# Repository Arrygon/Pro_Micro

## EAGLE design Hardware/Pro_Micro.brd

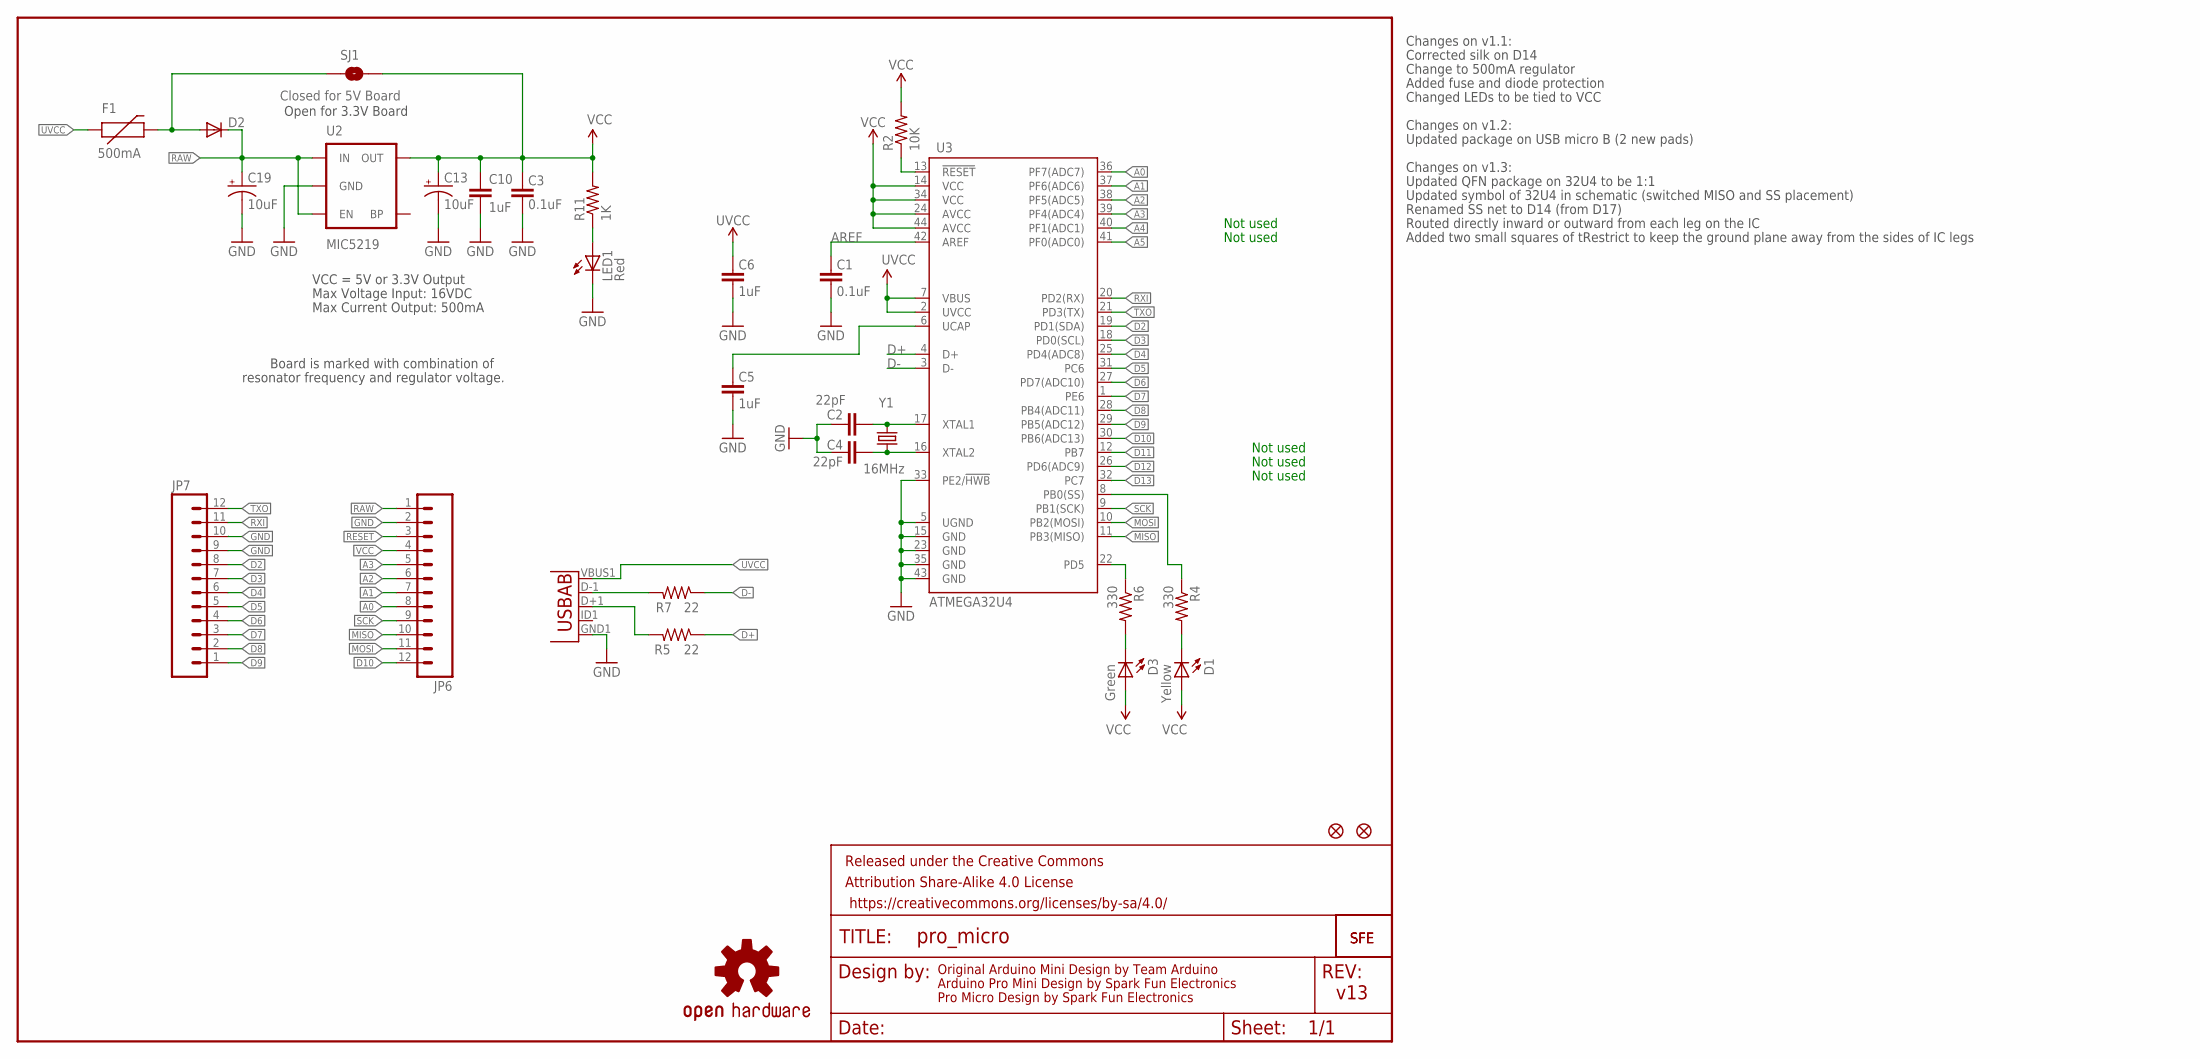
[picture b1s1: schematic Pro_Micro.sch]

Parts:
C1, C3: 0.1uF; 0603-CAP
C2, C4: 22pF; 0603-CAP
C5, C6, C10: 1uF; 0603-CAP
C13, C19: 10uF; EIA3216
D1: Yellow; LED-0603
D2: DIODESOD; SOD-323
D3: Green; LED-0603
F1: 500mA; PTC-1206
FRAME1: FRAME-LETTER; CREATIVE_COMMONS
JP1, JP2: FIDUCIALUFIDUCIAL; MICRO-FIDUCIAL
JP6, JP7: M12PTH; 1X12
LED1: Red; LED-0603
R2: 10K; 0603-RES
R4, R6: 330; 0603-RES
R5, R7: 22; 0603-RES
R11: 1K; 0603-RES
SJ1: Closed for 5V Board; SJ_2S
U2: MIC5219; SOT23-5
U3: ATMEGA32U4; QFN-44-NOPAD_1:1-LESS_PASTE
U$1: LOGO-SFESK; SFE-LOGO-FLAME
U$3: OSHW-LOGOS; OSHW-LOGO-S
U$11: LOGO-SFENEW; SFE-NEW-WEBLOGO
X1: USB-ABIN&OUT; USB-AB-MICRO-SMD-V03-IN&OUT
Y1: 16MHz; CRYSTAL-SMD-5X3

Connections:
A0: JP6.8, U3.36 (PF7(ADC7))
A1: JP6.7, U3.37 (PF6(ADC6))
A2: JP6.6, U3.38 (PF5(ADC5))
A3: JP6.5, U3.39 (PF4(ADC4))
A4: U3.40 (PF1(ADC1))
A5: U3.41 (PF0(ADC0))
AREF: C1.2, U3.42 (AREF)
D2: JP7.8, U3.19 (PD1(SDA))
D3: JP7.7, U3.18 (PD0(SCL))
D4: JP7.6, U3.25 (PD4(ADC8))
D5: JP7.5, U3.31 (PC6)
D6: JP7.4, U3.27 (PD7(ADC10))
D7: JP7.3, U3.1 (PE6)
D8: JP7.2, U3.28 (PB4(ADC11))
D9: JP7.1, U3.29 (PB5(ADC12))
D10: JP6.12, U3.30 (PB6(ADC13))
D11: U3.12 (PB7)
D12: U3.26 (PD6(ADC9))
D13: U3.32 (PC7)
D17: R4.1, U3.8 (PB0(SS))
D+: R5.1, U3.4 (D+)
D-: R7.1, U3.3 (D-)
GND: C1.1, C2.2, C3.1, C4.2, C5.1, C6.1, C10.2, C13.C (-), C19.C (-), JP6.2, JP7.9, JP7.10, LED1.C, U2.2 (GND), U3.5 (UGND), U3.15 (GND), U3.23 (GND), U3.33 (PE2/!HWB), U3.35 (GND), U3.43 (GND), X1.GND1 (GND)
MISO: JP6.10, U3.11 (PB3(MISO))
MOSI: JP6.11, U3.10 (PB2(MOSI))
unnamed: C4.1, U3.16 (XTAL2), Y1.1
unnamed: C2.1, U3.17 (XTAL1), Y1.3 (2)
unnamed: D2.2 (A), F1.2, SJ1.1
unnamed: C5.2, U3.6 (UCAP)
unnamed: D1.C, R4.2
unnamed: R7.2, X1.D-1 (D-)
unnamed: D3.C, R6.2
unnamed: R5.2, X1.D+1 (D+)
unnamed: LED1.A, R11.1
RAW: C19.A (+), D2.1 (C), JP6.1, U2.1 (IN), U2.3 (EN)
RESET: JP6.3, R2.1, U3.13 (!RESET)
RXI: JP7.11, U3.20 (PD2(RX))
SCK: JP6.9, U3.9 (PB1(SCK))
TXLED: R6.1, U3.22 (PD5)
TXO: JP7.12, U3.21 (PD3(TX))
UVCC: C6.2, F1.1, U3.2 (UVCC), U3.7 (VBUS), X1.VBUS1 (VBUS)
VCC: C3.2, C10.1, C13.A (+), D1.A, D3.A, JP6.4, R2.2, R11.2, SJ1.2, U2.5 (OUT), U3.14 (VCC), U3.24 (AVCC), U3.34 (VCC), U3.44 (AVCC)

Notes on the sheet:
Original Arduino Mini Design by Team Arduino
Arduino Pro Mini Design by Spark Fun Electronics
Max Voltage Input: 16VDC
Max Current Output: 500mA
Board is marked with combination of
resonator frequency and regulator voltage.
VCC = 5V or 3.3V Output
Not used
Pro Micro Design by Spark Fun Electronics
Changes on v1.1:
Corrected silk on D14
Change to 500mA regulator
Open for 3.3V Board
Added fuse and diode protection
Changed LEDs to be tied to VCC
Changes on v1.2:
Updated package on USB micro B (2 new pads)
Changes on v1.3:
Updated QFN package on 32U4 to be 1:1
Updated symbol of 32U4 in schematic (switched MISO and SS placement)
Renamed SS net to D14 (from D17)
Routed directly inward or outward from each leg on the IC
Added two small squares of tRestrict to keep the ground plane away from the sides of IC legs
v13

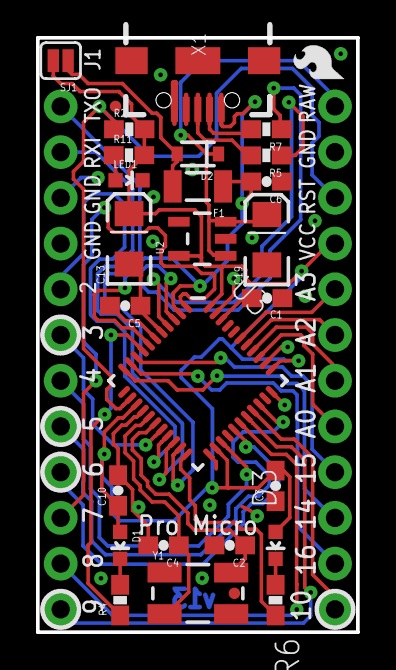
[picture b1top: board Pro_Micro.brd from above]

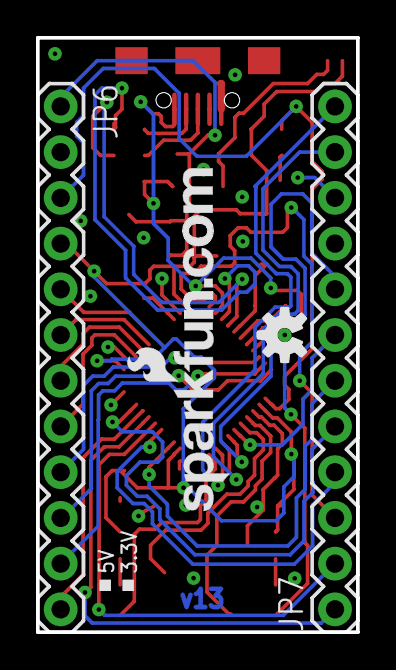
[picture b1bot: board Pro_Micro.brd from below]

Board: 2 copper layers, 17.8 x 33.0 mm, 33 parts (4 on the bottom side), 37 nets.

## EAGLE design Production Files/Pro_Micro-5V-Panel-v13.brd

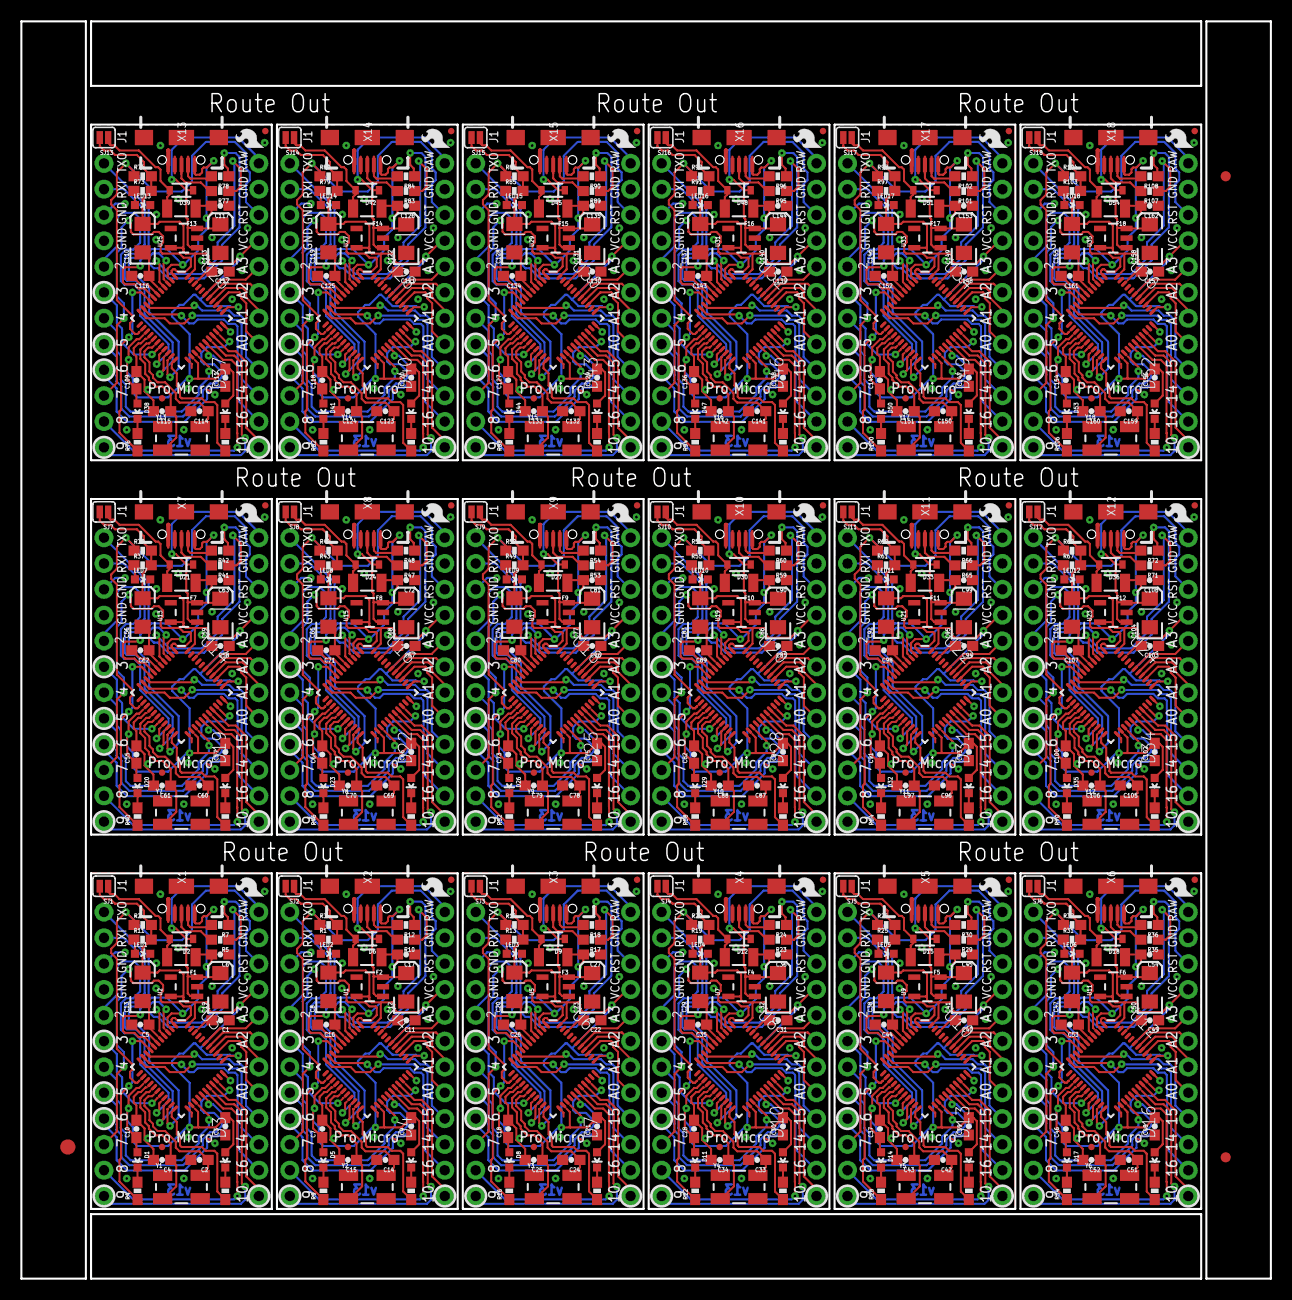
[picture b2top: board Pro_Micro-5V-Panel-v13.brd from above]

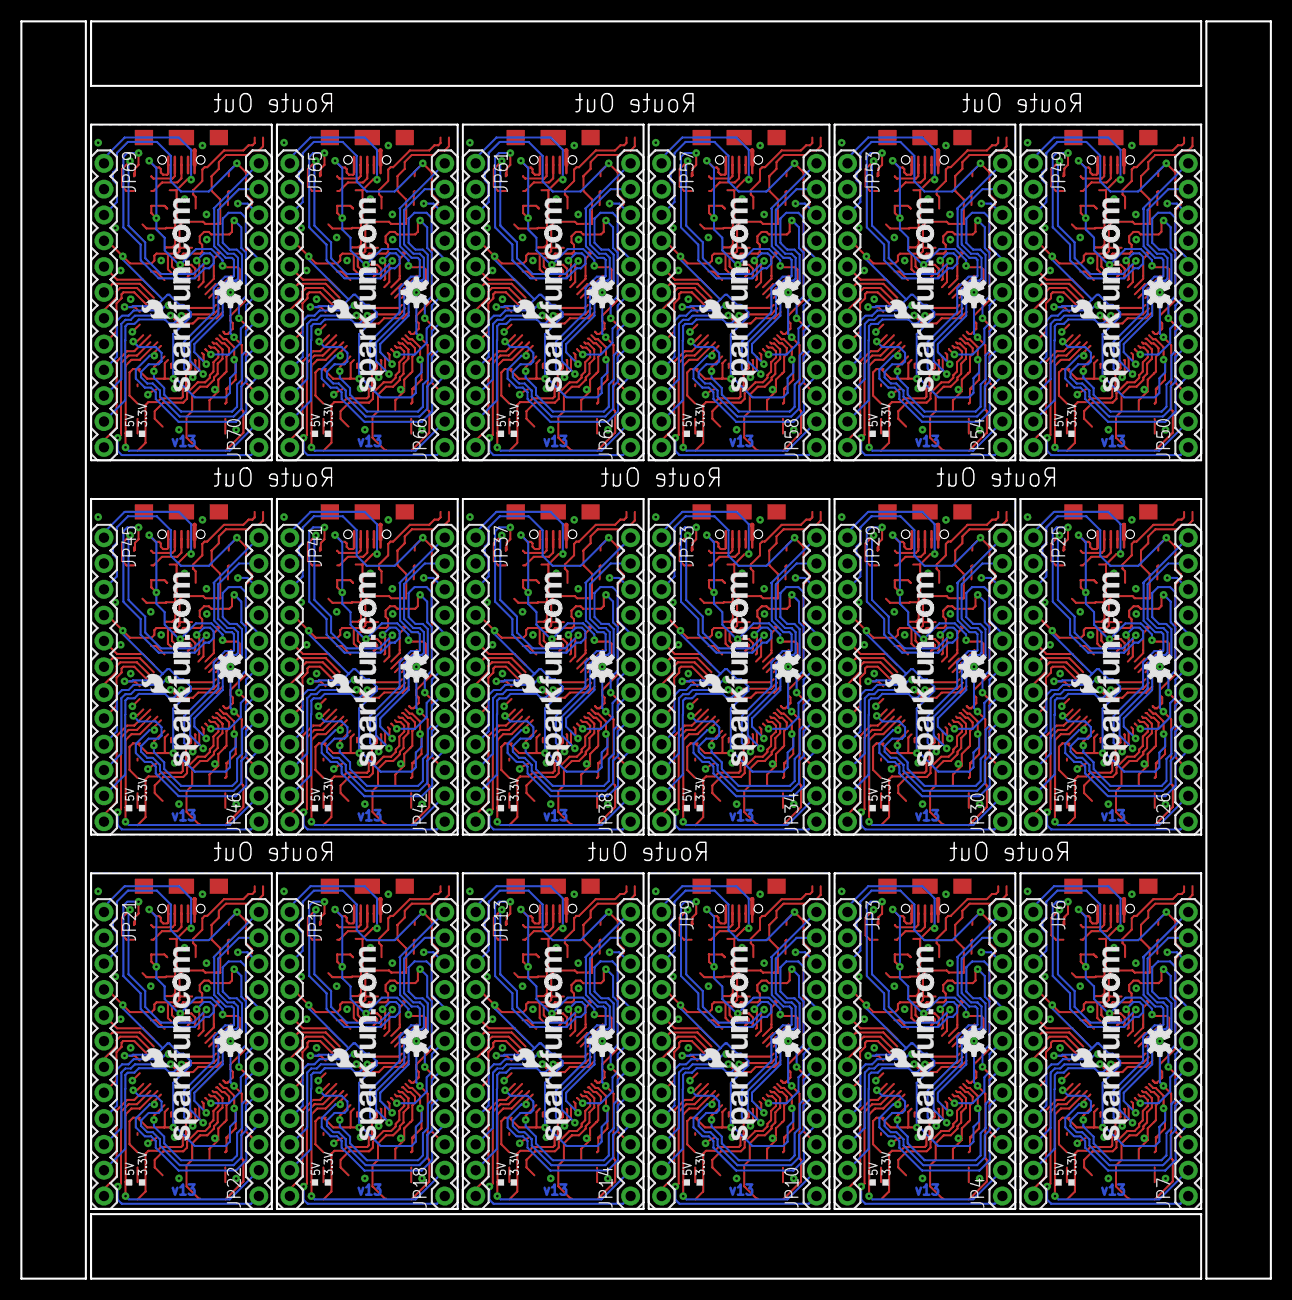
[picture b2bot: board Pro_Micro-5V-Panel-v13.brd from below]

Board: 2 copper layers, 122.9 x 123.7 mm, 579 parts (72 on the bottom side), 666 nets.

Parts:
C1, C3, C9, C11, C21, C22, C30, C31, C39, C40, C48, C49, C57, C58, C66, C67, C75, C76, C84, C85, C93, C94, C102, C103, C111, C112, C120, C121, C129, C130, C138, C139, C147, C148, C156, C157: 0.1uF; 0603-CAP
C2, C4, C14, C15, C24, C25, C33, C34, C42, C43, C51, C52, C60, C61, C69, C70, C78, C79, C87, C88, C96, C97, C105, C106, C114, C115, C123, C124, C132, C133, C141, C142, C150, C151, C159, C160: 22pF; 0603-CAP
C5, C6, C7, C10, C16, C17, C18, C26, C27, C28, C35, C36, C37, C44, C45, C46, C53, C54, C55, C62, C63, C64, C71, C72, C73, C80, C81, C82, C89, C90, C91, C98, C99, C100, C107, C108, C109, C116, C117, C118, C125, C126, C127, C134, C135, C136, C143, C144, C145, C152, C153, C154, C161, C162: 1uF; 0603-CAP
C8, C12, C13, C19, C20, C23, C29, C32, C38, C41, C47, C50, C56, C59, C65, C68, C74, C77, C83, C86, C92, C95, C101, C104, C110, C113, C119, C122, C128, C131, C137, C140, C146, C149, C155, C158: 10uF; EIA3216
D1, D5, D8, D11, D14, D17, D20, D23, D26, D29, D32, D35, D38, D41, D44, D47, D50, D53: Yellow; LED-0603
D2, D6, D9, D12, D15, D18, D21, D24, D27, D30, D33, D36, D39, D42, D45, D48, D51, D54: SOD-323
D3, D4, D7, D10, D13, D16, D19, D22, D25, D28, D31, D34, D37, D40, D43, D46, D49, D52: Green; LED-0603
E$1: FIDUCIAL-1.5X3
E$4, E$6: FIDUCIAL-1X2
F1, F2, F3, F4, F5, F6, F7, F8, F9, F10, F11, F12, F13, F14, F15, F16, F17, F18: 500mA; PTC-1206
JP1, JP2, JP5, JP8, JP11, JP12, JP15, JP16, JP19, JP20, JP23, JP24, JP27, JP28, JP31, JP32, JP35, JP36, JP39, JP40, JP43, JP44, JP47, JP48, JP51, JP52, JP55, JP56, JP59, JP60, JP63, JP64, JP67, JP68, JP71, JP72: FIDUCIALUFIDUCIAL; MICRO-FIDUCIAL
JP3, JP4, JP6, JP7, JP9, JP10, JP13, JP14, JP17, JP18, JP21, JP22, JP25, JP26, JP29, JP30, JP33, JP34, JP37, JP38, JP41, JP42, JP45, JP46, JP49, JP50, JP53, JP54, JP57, JP58, JP61, JP62, JP65, JP66, JP69, JP70: 1X12
LED1, LED2, LED3, LED4, LED5, LED6, LED7, LED8, LED9, LED10, LED11, LED12, LED13, LED14, LED15, LED16, LED17, LED18: Red; LED-0603
R1, R11, R13, R19, R25, R31, R37, R43, R49, R55, R61, R67, R73, R79, R85, R91, R97, R103: 1K; 0603-RES
R2, R3, R14, R20, R26, R32, R38, R44, R50, R56, R62, R68, R74, R80, R86, R92, R98, R104: 10K; 0603-RES
R4, R6, R8, R9, R15, R16, R21, R22, R27, R28, R33, R34, R39, R40, R45, R46, R51, R52, R57, R58, R63, R64, R69, R70, R75, R76, R81, R82, R87, R88, R93, R94, R99, R100, R105, R106: 330; 0603-RES
R5, R7, R10, R12, R17, R18, R23, R24, R29, R30, R35, R36, R41, R42, R47, R48, R53, R54, R59, R60, R65, R66, R71, R72, R77, R78, R83, R84, R89, R90, R95, R96, R101, R102, R107, R108: 22; 0603-RES
SJ1, SJ2, SJ3, SJ4, SJ5, SJ6, SJ7, SJ8, SJ9, SJ10, SJ11, SJ12, SJ13, SJ14, SJ15, SJ16, SJ17, SJ18: Closed for 5V Board; SJ_2S
U1, U2, U5, U7, U9, U11, U13, U15, U17, U19, U21, U23, U25, U27, U29, U31, U33, U35: MIC5219; SOT23-5
U3, U4, U6, U8, U10, U12, U14, U16, U18, U20, U22, U24, U26, U28, U30, U32, U34, U36: ATMEGA32U4; QFN-44-NOPAD_1:1-LESS_PASTE
U$1, U$4, U$7, U$10, U$14, U$17, U$20, U$23, U$26, U$29, U$32, U$35, U$38, U$41, U$44, U$47, U$50, U$53: LOGO-SFESK; SFE-LOGO-FLAME
U$2, U$6, U$9, U$11, U$13, U$16, U$19, U$22, U$25, U$28, U$31, U$34, U$37, U$40, U$43, U$46, U$49, U$52: LOGO-SFENEW; SFE-NEW-WEBLOGO
U$3, U$5, U$8, U$12, U$15, U$18, U$21, U$24, U$27, U$30, U$33, U$36, U$39, U$42, U$45, U$48, U$51, U$54: OSHW-LOGOS; OSHW-LOGO-S
X1, X2, X3, X4, X5, X6, X7, X8, X9, X10, X11, X12, X13, X14, X15, X16, X17, X18: USB-AB-MICRO-SMD-V03-IN&OUT
Y1, Y2, Y3, Y4, Y5, Y6, Y7, Y8, Y9, Y10, Y11, Y12, Y13, Y14, Y15, Y16, Y17, Y18: 16MHz; CRYSTAL-SMD-5X3

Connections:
A0: JP6.8, U3.36
A1: JP6.7, U3.37
A2: JP6.6, U3.38
A3: JP6.5, U3.39
A8: JP3.5, U4.39
A9: JP3.6, U4.38
A10: JP3.7, U4.37
A11: JP3.8, U4.36
A14: JP9.5, U6.39
A15: JP9.6, U6.38
A16: JP9.7, U6.37
A17: JP9.8, U6.36
A20: JP13.5, U8.39
A21: JP13.6, U8.38
A22: JP13.7, U8.37
A23: JP13.8, U8.36
A26: JP17.5, U10.39
A27: JP17.6, U10.38
A28: JP17.7, U10.37
A29: JP17.8, U10.36
A32: JP21.5, U12.39
A33: JP21.6, U12.38
A34: JP21.7, U12.37
A35: JP21.8, U12.36
A38: JP25.5, U14.39
A39: JP25.6, U14.38
A40: JP25.7, U14.37
A41: JP25.8, U14.36
A44: JP29.5, U16.39
A45: JP29.6, U16.38
A46: JP29.7, U16.37
A47: JP29.8, U16.36
A50: JP33.5, U18.39
A51: JP33.6, U18.38
A52: JP33.7, U18.37
A53: JP33.8, U18.36
A56: JP37.5, U20.39
A57: JP37.6, U20.38
A58: JP37.7, U20.37
A59: JP37.8, U20.36
A62: JP41.5, U22.39
A63: JP41.6, U22.38
A64: JP41.7, U22.37
A65: JP41.8, U22.36
A68: JP45.5, U24.39
A69: JP45.6, U24.38
A70: JP45.7, U24.37
A71: JP45.8, U24.36
A74: JP49.5, U26.39
A75: JP49.6, U26.38
A76: JP49.7, U26.37
A77: JP49.8, U26.36
A80: JP53.5, U28.39
A81: JP53.6, U28.38
A82: JP53.7, U28.37
A83: JP53.8, U28.36
A86: JP57.5, U30.39
A87: JP57.6, U30.38
A88: JP57.7, U30.37
A89: JP57.8, U30.36
A92: JP61.5, U32.39
A93: JP61.6, U32.38
A94: JP61.7, U32.37
A95: JP61.8, U32.36
A98: JP65.5, U34.39
A99: JP65.6, U34.38
A100: JP65.7, U34.37
A101: JP65.8, U34.36
A104: JP69.5, U36.39
A105: JP69.6, U36.38
A106: JP69.7, U36.37
A107: JP69.8, U36.36
AREF: C1.2, U3.42
AREF1: C11.2, U4.42
AREF2: C22.2, U6.42
AREF3: C31.2, U8.42
AREF4: C40.2, U10.42
AREF5: C49.2, U12.42
AREF6: C58.2, U14.42
AREF7: C67.2, U16.42
AREF8: C76.2, U18.42
AREF9: C85.2, U20.42
AREF10: C94.2, U22.42
AREF11: C103.2, U24.42
AREF12: C112.2, U26.42
AREF13: C121.2, U28.42
AREF14: C130.2, U30.42
AREF15: C139.2, U32.42
AREF16: C148.2, U34.42
AREF17: C157.2, U36.42
D1: JP4.1, U4.29
D2: JP7.8, U3.19
D3: JP7.7, U3.18
D4: JP7.6, U3.25
D5: JP7.5, U3.31
D6: JP7.4, U3.27
D7: JP7.3, U3.1
D8: JP7.2, U3.28
D9: JP7.1, U3.29
D10: JP6.12, U3.30
D14: R4.1, U3.8
D15: JP4.2, U4.28
D16: JP4.8, U4.19
D17: JP4.7, U4.18
D18: JP4.6, U4.25
D19: JP4.5, U4.31
D20: JP4.4, U4.27
D21: JP4.3, U4.1
D22: JP3.12, U4.30
D26: R9.1, U4.8
D27: JP10.1, U6.29
D28: JP10.2, U6.28
D29: JP10.8, U6.19
D30: JP10.7, U6.18
D31: JP10.6, U6.25
D32: JP10.5, U6.31
D33: JP10.4, U6.27
D34: JP10.3, U6.1
D35: JP9.12, U6.30
D39: R16.1, U6.8
D40: JP14.1, U8.29
D41: JP14.2, U8.28
D42: JP14.8, U8.19
D43: JP14.7, U8.18
D44: JP14.6, U8.25
D45: JP14.5, U8.31
D46: JP14.4, U8.27
D47: JP14.3, U8.1
D48: JP13.12, U8.30
D52: R22.1, U8.8
D53: JP18.1, U10.29
D54: JP18.2, U10.28
D55: JP18.8, U10.19
D56: JP18.7, U10.18
D57: JP18.6, U10.25
D58: JP18.5, U10.31
D59: JP18.4, U10.27
D60: JP18.3, U10.1
D61: JP17.12, U10.30
D65: R28.1, U10.8
D66: JP22.1, U12.29
D67: JP22.2, U12.28
D68: JP22.8, U12.19
D69: JP22.7, U12.18
D70: JP22.6, U12.25
D71: JP22.5, U12.31
D72: JP22.4, U12.27
D73: JP22.3, U12.1
D74: JP21.12, U12.30
D78: R34.1, U12.8
D79: JP26.1, U14.29
D80: JP26.2, U14.28
D81: JP26.8, U14.19
D82: JP26.7, U14.18
D83: JP26.6, U14.25
D84: JP26.5, U14.31
D85: JP26.4, U14.27
D86: JP26.3, U14.1
D87: JP25.12, U14.30
D91: R40.1, U14.8
D92: JP30.1, U16.29
D93: JP30.2, U16.28
D94: JP30.8, U16.19
D95: JP30.7, U16.18
D96: JP30.6, U16.25
D97: JP30.5, U16.31
D98: JP30.4, U16.27
D99: JP30.3, U16.1
D100: JP29.12, U16.30
D104: R46.1, U16.8
D105: JP34.1, U18.29
D106: JP34.2, U18.28
D107: JP34.8, U18.19
D108: JP34.7, U18.18
D109: JP34.6, U18.25
D110: JP34.5, U18.31
D111: JP34.4, U18.27
D112: JP34.3, U18.1
D113: JP33.12, U18.30
D117: R52.1, U18.8
D118: JP38.1, U20.29
D119: JP38.2, U20.28
D120: JP38.8, U20.19
D121: JP38.7, U20.18
D122: JP38.6, U20.25
D123: JP38.5, U20.31
D124: JP38.4, U20.27
D125: JP38.3, U20.1
D126: JP37.12, U20.30
D130: R58.1, U20.8
D131: JP42.1, U22.29
D132: JP42.2, U22.28
D133: JP42.8, U22.19
D134: JP42.7, U22.18
D135: JP42.6, U22.25
D136: JP42.5, U22.31
D137: JP42.4, U22.27
D138: JP42.3, U22.1
D139: JP41.12, U22.30
D143: R64.1, U22.8
D144: JP46.1, U24.29
D145: JP46.2, U24.28
D146: JP46.8, U24.19
D147: JP46.7, U24.18
D148: JP46.6, U24.25
D149: JP46.5, U24.31
D150: JP46.4, U24.27
D151: JP46.3, U24.1
D152: JP45.12, U24.30
D156: R70.1, U24.8
D157: JP50.1, U26.29
D158: JP50.2, U26.28
D159: JP50.8, U26.19
D160: JP50.7, U26.18
D161: JP50.6, U26.25
D162: JP50.5, U26.31
D163: JP50.4, U26.27
D164: JP50.3, U26.1
D165: JP49.12, U26.30
D169: R76.1, U26.8
D170: JP54.1, U28.29
D171: JP54.2, U28.28
D172: JP54.8, U28.19
D173: JP54.7, U28.18
D174: JP54.6, U28.25
D175: JP54.5, U28.31
D176: JP54.4, U28.27
D177: JP54.3, U28.1
D178: JP53.12, U28.30
D182: R82.1, U28.8
D183: JP58.1, U30.29
D184: JP58.2, U30.28
D185: JP58.8, U30.19
D186: JP58.7, U30.18
D187: JP58.6, U30.25
D188: JP58.5, U30.31
D189: JP58.4, U30.27
D190: JP58.3, U30.1
D191: JP57.12, U30.30
D195: R88.1, U30.8
D196: JP62.1, U32.29
D197: JP62.2, U32.28
D198: JP62.8, U32.19
D199: JP62.7, U32.18
D200: JP62.6, U32.25
D201: JP62.5, U32.31
D202: JP62.4, U32.27
D203: JP62.3, U32.1
D204: JP61.12, U32.30
D208: R94.1, U32.8
D209: JP66.1, U34.29
D210: JP66.2, U34.28
D211: JP66.8, U34.19
D212: JP66.7, U34.18
D213: JP66.6, U34.25
D214: JP66.5, U34.31
D215: JP66.4, U34.27
D216: JP66.3, U34.1
D217: JP65.12, U34.30
D221: R100.1, U34.8
D222: JP70.1, U36.29
D223: JP70.2, U36.28
D224: JP70.8, U36.19
D225: JP70.7, U36.18
D226: JP70.6, U36.25
D227: JP70.5, U36.31
D228: JP70.4, U36.27
D229: JP70.3, U36.1
D230: JP69.12, U36.30
D234: R106.1, U36.8
D+: R5.1, U3.4
D+1: R10.1, U4.4
D+2: R17.1, U6.4
D+3: R23.1, U8.4
D+4: R29.1, U10.4
D+5: R35.1, U12.4
D+6: R41.1, U14.4
D+7: R47.1, U16.4
D+8: R53.1, U18.4
D+9: R59.1, U20.4
D+10: R65.1, U22.4
D+11: R71.1, U24.4
D+12: R77.1, U26.4
D+13: R83.1, U28.4
D+14: R89.1, U30.4
D+15: R95.1, U32.4
D+16: R101.1, U34.4
D+17: R107.1, U36.4
D-: R7.1, U3.3
D-1: R12.1, U4.3
D-2: R18.1, U6.3
D-3: R24.1, U8.3
D-4: R30.1, U10.3
D-5: R36.1, U12.3
D-6: R42.1, U14.3
D-7: R48.1, U16.3
D-8: R54.1, U18.3
D-9: R60.1, U20.3
D-10: R66.1, U22.3
D-11: R72.1, U24.3
D-12: R78.1, U26.3
D-13: R84.1, U28.3
D-14: R90.1, U30.3
D-15: R96.1, U32.3
D-16: R102.1, U34.3
D-17: R108.1, U36.3
GND: C1.1, C2.2, C3.1, C4.2, C5.1, C6.1, C10.2, C13.C, C19.C, JP6.2, JP7.9, JP7.10, LED1.C, U2.2, U3.5, U3.15, U3.23, U3.33, U3.35, U3.43, X1.GND1
GND1: C7.2, C8.C, C9.1, C11.1, C12.C, C14.2, C15.2, C16.1, C17.1, JP3.2, JP4.9, JP4.10, LED2.C, U1.2, U4.5, U4.15, U4.23, U4.33, U4.35, U4.43, X2.GND1
GND2: C18.2, C20.C, C21.1, C22.1, C23.C, C24.2, C25.2, C26.1, C27.1, JP9.2, JP10.9, JP10.10, LED3.C, U5.2, U6.5, U6.15, U6.23, U6.33, U6.35, U6.43, X3.GND1
GND3: C28.2, C29.C, C30.1, C31.1, C32.C, C33.2, C34.2, C35.1, C36.1, JP13.2, JP14.9, JP14.10, LED4.C, U7.2, U8.5, U8.15, U8.23, U8.33, U8.35, U8.43, X4.GND1
GND4: C37.2, C38.C, C39.1, C40.1, C41.C, C42.2, C43.2, C44.1, C45.1, JP17.2, JP18.9, JP18.10, LED5.C, U9.2, U10.5, U10.15, U10.23, U10.33, U10.35, U10.43, X5.GND1
GND5: C46.2, C47.C, C48.1, C49.1, C50.C, C51.2, C52.2, C53.1, C54.1, JP21.2, JP22.9, JP22.10, LED6.C, U11.2, U12.5, U12.15, U12.23, U12.33, U12.35, U12.43, X6.GND1
GND6: C55.2, C56.C, C57.1, C58.1, C59.C, C60.2, C61.2, C62.1, C63.1, JP25.2, JP26.9, JP26.10, LED7.C, U13.2, U14.5, U14.15, U14.23, U14.33, U14.35, U14.43, X7.GND1
GND7: C64.2, C65.C, C66.1, C67.1, C68.C, C69.2, C70.2, C71.1, C72.1, JP29.2, JP30.9, JP30.10, LED8.C, U15.2, U16.5, U16.15, U16.23, U16.33, U16.35, U16.43, X8.GND1
GND8: C73.2, C74.C, C75.1, C76.1, C77.C, C78.2, C79.2, C80.1, C81.1, JP33.2, JP34.9, JP34.10, LED9.C, U17.2, U18.5, U18.15, U18.23, U18.33, U18.35, U18.43, X9.GND1
GND9: C82.2, C83.C, C84.1, C85.1, C86.C, C87.2, C88.2, C89.1, C90.1, JP37.2, JP38.9, JP38.10, LED10.C, U19.2, U20.5, U20.15, U20.23, U20.33, U20.35, U20.43, X10.GND1
GND10: C91.2, C92.C, C93.1, C94.1, C95.C, C96.2, C97.2, C98.1, C99.1, JP41.2, JP42.9, JP42.10, LED11.C, U21.2, U22.5, U22.15, U22.23, U22.33, U22.35, U22.43, X11.GND1
GND11: C100.2, C101.C, C102.1, C103.1, C104.C, C105.2, C106.2, C107.1, C108.1, JP45.2, JP46.9, JP46.10, LED12.C, U23.2, U24.5, U24.15, U24.23, U24.33, U24.35, U24.43, X12.GND1
GND12: C109.2, C110.C, C111.1, C112.1, C113.C, C114.2, C115.2, C116.1, C117.1, JP49.2, JP50.9, JP50.10, LED13.C, U25.2, U26.5, U26.15, U26.23, U26.33, U26.35, U26.43, X13.GND1
GND13: C118.2, C119.C, C120.1, C121.1, C122.C, C123.2, C124.2, C125.1, C126.1, JP53.2, JP54.9, JP54.10, LED14.C, U27.2, U28.5, U28.15, U28.23, U28.33, U28.35, U28.43, X14.GND1
GND14: C127.2, C128.C, C129.1, C130.1, C131.C, C132.2, C133.2, C134.1, C135.1, JP57.2, JP58.9, JP58.10, LED15.C, U29.2, U30.5, U30.15, U30.23, U30.33, U30.35, U30.43, X15.GND1
GND15: C136.2, C137.C, C138.1, C139.1, C140.C, C141.2, C142.2, C143.1, C144.1, JP61.2, JP62.9, JP62.10, LED16.C, U31.2, U32.5, U32.15, U32.23, U32.33, U32.35, U32.43, X16.GND1
GND16: C145.2, C146.C, C147.1, C148.1, C149.C, C150.2, C151.2, C152.1, C153.1, JP65.2, JP66.9, JP66.10, LED17.C, U33.2, U34.5, U34.15, U34.23, U34.33, U34.35, U34.43, X17.GND1
GND17: C154.2, C155.C, C156.1, C157.1, C158.C, C159.2, C160.2, C161.1, C162.1, JP69.2, JP70.9, JP70.10, LED18.C, U35.2, U36.5, U36.15, U36.23, U36.33, U36.35, U36.43, X18.GND1
MISO: JP6.10, U3.11
MISO1: JP3.10, U4.11
MISO2: JP9.10, U6.11
MISO3: JP13.10, U8.11
MISO4: JP17.10, U10.11
MISO5: JP21.10, U12.11
MISO6: JP25.10, U14.11
MISO7: JP29.10, U16.11
MISO8: JP33.10, U18.11
MISO9: JP37.10, U20.11
MISO10: JP41.10, U22.11
MISO11: JP45.10, U24.11
MISO12: JP49.10, U26.11
MISO13: JP53.10, U28.11
MISO14: JP57.10, U30.11
MISO15: JP61.10, U32.11
MISO16: JP65.10, U34.11
MISO17: JP69.10, U36.11
MOSI: JP6.11, U3.10
MOSI1: JP3.11, U4.10
MOSI2: JP9.11, U6.10
MOSI3: JP13.11, U8.10
MOSI4: JP17.11, U10.10
MOSI5: JP21.11, U12.10
MOSI6: JP25.11, U14.10
MOSI7: JP29.11, U16.10
MOSI8: JP33.11, U18.10
MOSI9: JP37.11, U20.10
MOSI10: JP41.11, U22.10
MOSI11: JP45.11, U24.10
MOSI12: JP49.11, U26.10
MOSI13: JP53.11, U28.10
MOSI14: JP57.11, U30.10
MOSI15: JP61.11, U32.10
MOSI16: JP65.11, U34.10
MOSI17: JP69.11, U36.10
unnamed: C4.1, U3.16, Y1.1
unnamed: C2.1, U3.17, Y1.3
unnamed: D2.2, F1.2, SJ1.1
unnamed: C5.2, U3.6
unnamed: D1.C, R4.2
unnamed: R7.2, X1.D-1
unnamed: D3.C, R6.2
unnamed: R5.2, X1.D+1
unnamed: LED2.A, R1.1
unnamed: C15.1, U4.16, Y2.1
unnamed: C14.1, U4.17, Y2.3
unnamed: C16.2, U4.6
unnamed: R12.2, X2.D-1
unnamed: R10.2, X2.D+1
unnamed: D6.2, F2.2, SJ2.1
unnamed: D5.C, R9.2
unnamed: D4.C, R8.2
unnamed: LED3.A, R13.1
unnamed: C25.1, U6.16, Y3.1
unnamed: C24.1, U6.17, Y3.3
unnamed: C26.2, U6.6
unnamed: R18.2, X3.D-1
unnamed: R17.2, X3.D+1
unnamed: D9.2, F3.2, SJ3.1
unnamed: D8.C, R16.2
unnamed: D7.C, R15.2
unnamed: LED4.A, R19.1
unnamed: C34.1, U8.16, Y4.1
unnamed: C33.1, U8.17, Y4.3
unnamed: C35.2, U8.6
unnamed: R24.2, X4.D-1
unnamed: R23.2, X4.D+1
unnamed: D12.2, F4.2, SJ4.1
unnamed: D11.C, R22.2
unnamed: D10.C, R21.2
unnamed: LED5.A, R25.1
unnamed: C43.1, U10.16, Y5.1
unnamed: LED1.A, R11.1
unnamed: C42.1, U10.17, Y5.3
unnamed: C44.2, U10.6
unnamed: R30.2, X5.D-1
unnamed: R29.2, X5.D+1
unnamed: D15.2, F5.2, SJ5.1
unnamed: D14.C, R28.2
unnamed: D13.C, R27.2
unnamed: LED6.A, R31.1
unnamed: C52.1, U12.16, Y6.1
unnamed: C51.1, U12.17, Y6.3
unnamed: C53.2, U12.6
unnamed: R36.2, X6.D-1
unnamed: R35.2, X6.D+1
unnamed: D18.2, F6.2, SJ6.1
unnamed: D17.C, R34.2
unnamed: D16.C, R33.2
unnamed: LED7.A, R37.1
unnamed: C61.1, U14.16, Y7.1
unnamed: C60.1, U14.17, Y7.3
unnamed: C62.2, U14.6
unnamed: R42.2, X7.D-1
unnamed: R41.2, X7.D+1
unnamed: D21.2, F7.2, SJ7.1
unnamed: D20.C, R40.2
unnamed: D19.C, R39.2
unnamed: LED8.A, R43.1
unnamed: C70.1, U16.16, Y8.1
unnamed: C69.1, U16.17, Y8.3
unnamed: C71.2, U16.6
unnamed: R48.2, X8.D-1
unnamed: R47.2, X8.D+1
unnamed: D24.2, F8.2, SJ8.1
unnamed: D23.C, R46.2
unnamed: D22.C, R45.2
unnamed: LED9.A, R49.1
unnamed: C79.1, U18.16, Y9.1
unnamed: C78.1, U18.17, Y9.3
unnamed: C80.2, U18.6
unnamed: R54.2, X9.D-1
unnamed: R53.2, X9.D+1
unnamed: D27.2, F9.2, SJ9.1
unnamed: D26.C, R52.2
unnamed: D25.C, R51.2
unnamed: LED10.A, R55.1
unnamed: C88.1, U20.16, Y10.1
unnamed: C87.1, U20.17, Y10.3
unnamed: C89.2, U20.6
unnamed: R60.2, X10.D-1
unnamed: R59.2, X10.D+1
unnamed: D30.2, F10.2, SJ10.1
unnamed: D29.C, R58.2
unnamed: D28.C, R57.2
unnamed: LED11.A, R61.1
unnamed: C97.1, U22.16, Y11.1
unnamed: C96.1, U22.17, Y11.3
unnamed: C98.2, U22.6
unnamed: R66.2, X11.D-1
unnamed: R65.2, X11.D+1
unnamed: D33.2, F11.2, SJ11.1
unnamed: D32.C, R64.2
unnamed: D31.C, R63.2
unnamed: LED12.A, R67.1
unnamed: C106.1, U24.16, Y12.1
unnamed: C105.1, U24.17, Y12.3
unnamed: C107.2, U24.6
unnamed: R72.2, X12.D-1
unnamed: R71.2, X12.D+1
unnamed: D36.2, F12.2, SJ12.1
unnamed: D35.C, R70.2
unnamed: D34.C, R69.2
unnamed: LED13.A, R73.1
unnamed: C115.1, U26.16, Y13.1
unnamed: C114.1, U26.17, Y13.3
unnamed: C116.2, U26.6
unnamed: R78.2, X13.D-1
unnamed: R77.2, X13.D+1
unnamed: D39.2, F13.2, SJ13.1
unnamed: D38.C, R76.2
unnamed: D37.C, R75.2
unnamed: LED14.A, R79.1
unnamed: C124.1, U28.16, Y14.1
unnamed: C123.1, U28.17, Y14.3
unnamed: C125.2, U28.6
unnamed: R84.2, X14.D-1
unnamed: R83.2, X14.D+1
unnamed: D42.2, F14.2, SJ14.1
unnamed: D41.C, R82.2
unnamed: D40.C, R81.2
unnamed: LED15.A, R85.1
unnamed: C133.1, U30.16, Y15.1
unnamed: C132.1, U30.17, Y15.3
unnamed: C134.2, U30.6
unnamed: R90.2, X15.D-1
unnamed: R89.2, X15.D+1
unnamed: D45.2, F15.2, SJ15.1
unnamed: D44.C, R88.2
unnamed: D43.C, R87.2
unnamed: LED16.A, R91.1
unnamed: C142.1, U32.16, Y16.1
unnamed: C141.1, U32.17, Y16.3
unnamed: C143.2, U32.6
unnamed: R96.2, X16.D-1
unnamed: R95.2, X16.D+1
unnamed: D48.2, F16.2, SJ16.1
unnamed: D47.C, R94.2
unnamed: D46.C, R93.2
unnamed: LED17.A, R97.1
unnamed: C151.1, U34.16, Y17.1
unnamed: C150.1, U34.17, Y17.3
unnamed: C152.2, U34.6
unnamed: R102.2, X17.D-1
unnamed: R101.2, X17.D+1
unnamed: D51.2, F17.2, SJ17.1
unnamed: D50.C, R100.2
unnamed: D49.C, R99.2
unnamed: LED18.A, R103.1
unnamed: C160.1, U36.16, Y18.1
unnamed: C159.1, U36.17, Y18.3
unnamed: C161.2, U36.6
unnamed: R108.2, X18.D-1
unnamed: R107.2, X18.D+1
unnamed: D54.2, F18.2, SJ18.1
unnamed: D53.C, R106.2
unnamed: D52.C, R105.2
RAW: C19.A, D2.1, JP6.1, U2.1, U2.3
RAW1: C12.A, D6.1, JP3.1, U1.1, U1.3
RAW2: C23.A, D9.1, JP9.1, U5.1, U5.3
RAW3: C32.A, D12.1, JP13.1, U7.1, U7.3
RAW4: C41.A, D15.1, JP17.1, U9.1, U9.3
RAW5: C50.A, D18.1, JP21.1, U11.1, U11.3
RAW6: C59.A, D21.1, JP25.1, U13.1, U13.3
RAW7: C68.A, D24.1, JP29.1, U15.1, U15.3
RAW8: C77.A, D27.1, JP33.1, U17.1, U17.3
RAW9: C86.A, D30.1, JP37.1, U19.1, U19.3
RAW10: C95.A, D33.1, JP41.1, U21.1, U21.3
RAW11: C104.A, D36.1, JP45.1, U23.1, U23.3
RAW12: C113.A, D39.1, JP49.1, U25.1, U25.3
RAW13: C122.A, D42.1, JP53.1, U27.1, U27.3
RAW14: C131.A, D45.1, JP57.1, U29.1, U29.3
RAW15: C140.A, D48.1, JP61.1, U31.1, U31.3
RAW16: C149.A, D51.1, JP65.1, U33.1, U33.3
RAW17: C158.A, D54.1, JP69.1, U35.1, U35.3
RESET: JP6.3, R2.1, U3.13
RESET1: JP3.3, R3.1, U4.13
RESET2: JP9.3, R14.1, U6.13
RESET3: JP13.3, R20.1, U8.13
RESET4: JP17.3, R26.1, U10.13
RESET5: JP21.3, R32.1, U12.13
RESET6: JP25.3, R38.1, U14.13
RESET7: JP29.3, R44.1, U16.13
RESET8: JP33.3, R50.1, U18.13
RESET9: JP37.3, R56.1, U20.13
RESET10: JP41.3, R62.1, U22.13
RESET11: JP45.3, R68.1, U24.13
RESET12: JP49.3, R74.1, U26.13
RESET13: JP53.3, R80.1, U28.13
RESET14: JP57.3, R86.1, U30.13
RESET15: JP61.3, R92.1, U32.13
RESET16: JP65.3, R98.1, U34.13
RESET17: JP69.3, R104.1, U36.13
RXI: JP7.11, U3.20
RXI1: JP4.11, U4.20
RXI2: JP10.11, U6.20
RXI3: JP14.11, U8.20
RXI4: JP18.11, U10.20
RXI5: JP22.11, U12.20
RXI6: JP26.11, U14.20
RXI7: JP30.11, U16.20
RXI8: JP34.11, U18.20
RXI9: JP38.11, U20.20
RXI10: JP42.11, U22.20
RXI11: JP46.11, U24.20
RXI12: JP50.11, U26.20
RXI13: JP54.11, U28.20
RXI14: JP58.11, U30.20
RXI15: JP62.11, U32.20
RXI16: JP66.11, U34.20
RXI17: JP70.11, U36.20
SCK: JP6.9, U3.9
SCK1: JP3.9, U4.9
SCK2: JP9.9, U6.9
SCK3: JP13.9, U8.9
SCK4: JP17.9, U10.9
SCK5: JP21.9, U12.9
SCK6: JP25.9, U14.9
SCK7: JP29.9, U16.9
SCK8: JP33.9, U18.9
SCK9: JP37.9, U20.9
SCK10: JP41.9, U22.9
SCK11: JP45.9, U24.9
SCK12: JP49.9, U26.9
SCK13: JP53.9, U28.9
SCK14: JP57.9, U30.9
SCK15: JP61.9, U32.9
SCK16: JP65.9, U34.9
SCK17: JP69.9, U36.9
TXLED: R6.1, U3.22
TXLED1: R8.1, U4.22
TXLED2: R15.1, U6.22
TXLED3: R21.1, U8.22
TXLED4: R27.1, U10.22
TXLED5: R33.1, U12.22
TXLED6: R39.1, U14.22
TXLED7: R45.1, U16.22
TXLED8: R51.1, U18.22
TXLED9: R57.1, U20.22
TXLED10: R63.1, U22.22
TXLED11: R69.1, U24.22
TXLED12: R75.1, U26.22
TXLED13: R81.1, U28.22
TXLED14: R87.1, U30.22
TXLED15: R93.1, U32.22
TXLED16: R99.1, U34.22
TXLED17: R105.1, U36.22
TXO: JP7.12, U3.21
TXO1: JP4.12, U4.21
TXO2: JP10.12, U6.21
TXO3: JP14.12, U8.21
TXO4: JP18.12, U10.21
TXO5: JP22.12, U12.21
TXO6: JP26.12, U14.21
TXO7: JP30.12, U16.21
TXO8: JP34.12, U18.21
TXO9: JP38.12, U20.21
TXO10: JP42.12, U22.21
TXO11: JP46.12, U24.21
TXO12: JP50.12, U26.21
TXO13: JP54.12, U28.21
TXO14: JP58.12, U30.21
TXO15: JP62.12, U32.21
TXO16: JP66.12, U34.21
TXO17: JP70.12, U36.21
UVCC: C6.2, F1.1, U3.2, U3.7, X1.VBUS1
UVCC1: C17.2, F2.1, U4.2, U4.7, X2.VBUS1
UVCC2: C27.2, F3.1, U6.2, U6.7, X3.VBUS1
UVCC3: C36.2, F4.1, U8.2, U8.7, X4.VBUS1
UVCC4: C45.2, F5.1, U10.2, U10.7, X5.VBUS1
UVCC5: C54.2, F6.1, U12.2, U12.7, X6.VBUS1
UVCC6: C63.2, F7.1, U14.2, U14.7, X7.VBUS1
UVCC7: C72.2, F8.1, U16.2, U16.7, X8.VBUS1
UVCC8: C81.2, F9.1, U18.2, U18.7, X9.VBUS1
UVCC9: C90.2, F10.1, U20.2, U20.7, X10.VBUS1
UVCC10: C99.2, F11.1, U22.2, U22.7, X11.VBUS1
UVCC11: C108.2, F12.1, U24.2, U24.7, X12.VBUS1
UVCC12: C117.2, F13.1, U26.2, U26.7, X13.VBUS1
UVCC13: C126.2, F14.1, U28.2, U28.7, X14.VBUS1
UVCC14: C135.2, F15.1, U30.2, U30.7, X15.VBUS1
UVCC15: C144.2, F16.1, U32.2, U32.7, X16.VBUS1
UVCC16: C153.2, F17.1, U34.2, U34.7, X17.VBUS1
UVCC17: C162.2, F18.1, U36.2, U36.7, X18.VBUS1
VCC: C3.2, C10.1, C13.A, D1.A, D3.A, JP6.4, R2.2, R11.2, SJ1.2, U2.5, U3.14, U3.24, U3.34, U3.44
VCC1: C7.1, C8.A, C9.2, D4.A, D5.A, JP3.4, R1.2, R3.2, SJ2.2, U1.5, U4.14, U4.24, U4.34, U4.44
VCC2: C18.1, C20.A, C21.2, D7.A, D8.A, JP9.4, R13.2, R14.2, SJ3.2, U5.5, U6.14, U6.24, U6.34, U6.44
VCC3: C28.1, C29.A, C30.2, D10.A, D11.A, JP13.4, R19.2, R20.2, SJ4.2, U7.5, U8.14, U8.24, U8.34, U8.44
VCC4: C37.1, C38.A, C39.2, D13.A, D14.A, JP17.4, R25.2, R26.2, SJ5.2, U9.5, U10.14, U10.24, U10.34, U10.44
VCC5: C46.1, C47.A, C48.2, D16.A, D17.A, JP21.4, R31.2, R32.2, SJ6.2, U11.5, U12.14, U12.24, U12.34, U12.44
VCC6: C55.1, C56.A, C57.2, D19.A, D20.A, JP25.4, R37.2, R38.2, SJ7.2, U13.5, U14.14, U14.24, U14.34, U14.44
VCC7: C64.1, C65.A, C66.2, D22.A, D23.A, JP29.4, R43.2, R44.2, SJ8.2, U15.5, U16.14, U16.24, U16.34, U16.44
VCC8: C73.1, C74.A, C75.2, D25.A, D26.A, JP33.4, R49.2, R50.2, SJ9.2, U17.5, U18.14, U18.24, U18.34, U18.44
VCC9: C82.1, C83.A, C84.2, D28.A, D29.A, JP37.4, R55.2, R56.2, SJ10.2, U19.5, U20.14, U20.24, U20.34, U20.44
VCC10: C91.1, C92.A, C93.2, D31.A, D32.A, JP41.4, R61.2, R62.2, SJ11.2, U21.5, U22.14, U22.24, U22.34, U22.44
VCC11: C100.1, C101.A, C102.2, D34.A, D35.A, JP45.4, R67.2, R68.2, SJ12.2, U23.5, U24.14, U24.24, U24.34, U24.44
VCC12: C109.1, C110.A, C111.2, D37.A, D38.A, JP49.4, R73.2, R74.2, SJ13.2, U25.5, U26.14, U26.24, U26.34, U26.44
VCC13: C118.1, C119.A, C120.2, D40.A, D41.A, JP53.4, R79.2, R80.2, SJ14.2, U27.5, U28.14, U28.24, U28.34, U28.44
VCC14: C127.1, C128.A, C129.2, D43.A, D44.A, JP57.4, R85.2, R86.2, SJ15.2, U29.5, U30.14, U30.24, U30.34, U30.44
VCC15: C136.1, C137.A, C138.2, D46.A, D47.A, JP61.4, R91.2, R92.2, SJ16.2, U31.5, U32.14, U32.24, U32.34, U32.44
VCC16: C145.1, C146.A, C147.2, D49.A, D50.A, JP65.4, R97.2, R98.2, SJ17.2, U33.5, U34.14, U34.24, U34.34, U34.44
VCC17: C154.1, C155.A, C156.2, D52.A, D53.A, JP69.4, R103.2, R104.2, SJ18.2, U35.5, U36.14, U36.24, U36.34, U36.44

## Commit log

2013-10-18 Changed jumper package to normally open
    Open Jumper = 3.3V logic
    also added gitignore
2013-10-18 ignore gerbers and zip files
2013-11-14 repositioned fiducials and one via
    It used to be under the crystal.
2013-11-14 add ignore, moved fiductials and one via
    one fid used to be under crystal
2013-11-14 Created Panel
2014-03-26 changed tcream on ATmega32U4 to "less paste"
2015-06-19 Updated to current library parts with correct labels. Changed silk to vector font. Moved a few bits of silk to not be over vias. Aligned angled traces to 45 degrees

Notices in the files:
parts and their libraries:
SparkFun-Aesthetics: Licensing: CC v3.0 Share-Alike You are welcome to use this library for commercial purposes.
SparkFun-Aesthetics: Released under the Creative Commons Attribution Share-Alike 4.0 License
SparkFun-Aesthetics: https://creativecommons.org/licenses/by-sa/4.0
